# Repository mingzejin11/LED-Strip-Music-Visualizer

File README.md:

# LED-Strip-Music-Visualizer
Converting some boring LED strips into a party starter :)

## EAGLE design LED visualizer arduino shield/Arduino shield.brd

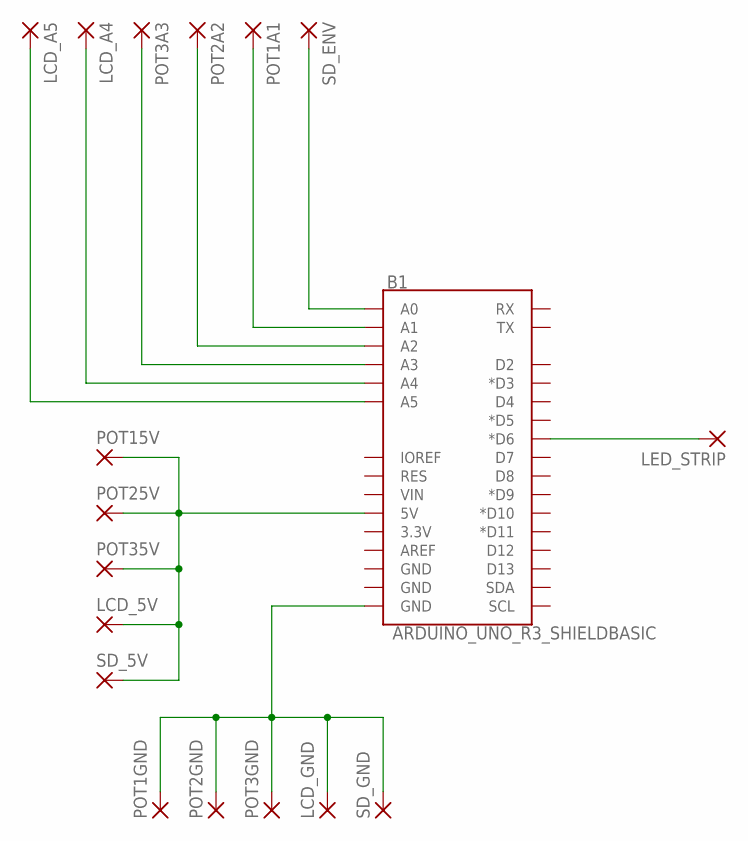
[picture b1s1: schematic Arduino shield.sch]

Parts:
B1: ARDUINO_UNO_R3_SHIELDBASIC; UNO_R3_SHIELD
LCD_5V: 1,6/0,9
LCD_A4, LCD_A5: 1,6/0,9
LCD_GND: 1,6/0,9
LED_STRIP: 1,6/0,9
POT1A1, POT1GND, POT2A2, POT2GND, POT3A3, POT3GND, POT15V, POT25V, POT35V: 1,6/0,9
SD_5V: 1,6/0,9
SD_ENV: 1,6/0,9
SD_GND: 1,6/0,9

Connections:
unnamed: B1.A0, SD_ENV.1
unnamed: B1.A1, POT1A1.1
unnamed: B1.A2, POT2A2.1
unnamed: B1.A3, POT3A3.1
unnamed: B1.A4, LCD_A4.1
unnamed: B1.A5, LCD_A5.1
unnamed: B1.GND@0 (GND), LCD_GND.1, POT1GND.1, POT2GND.1, POT3GND.1, SD_GND.1
unnamed: B1.5V, LCD_5V.1, POT15V.1, POT25V.1, POT35V.1, SD_5V.1
unnamed: B1.D6 (*D6), LED_STRIP.1

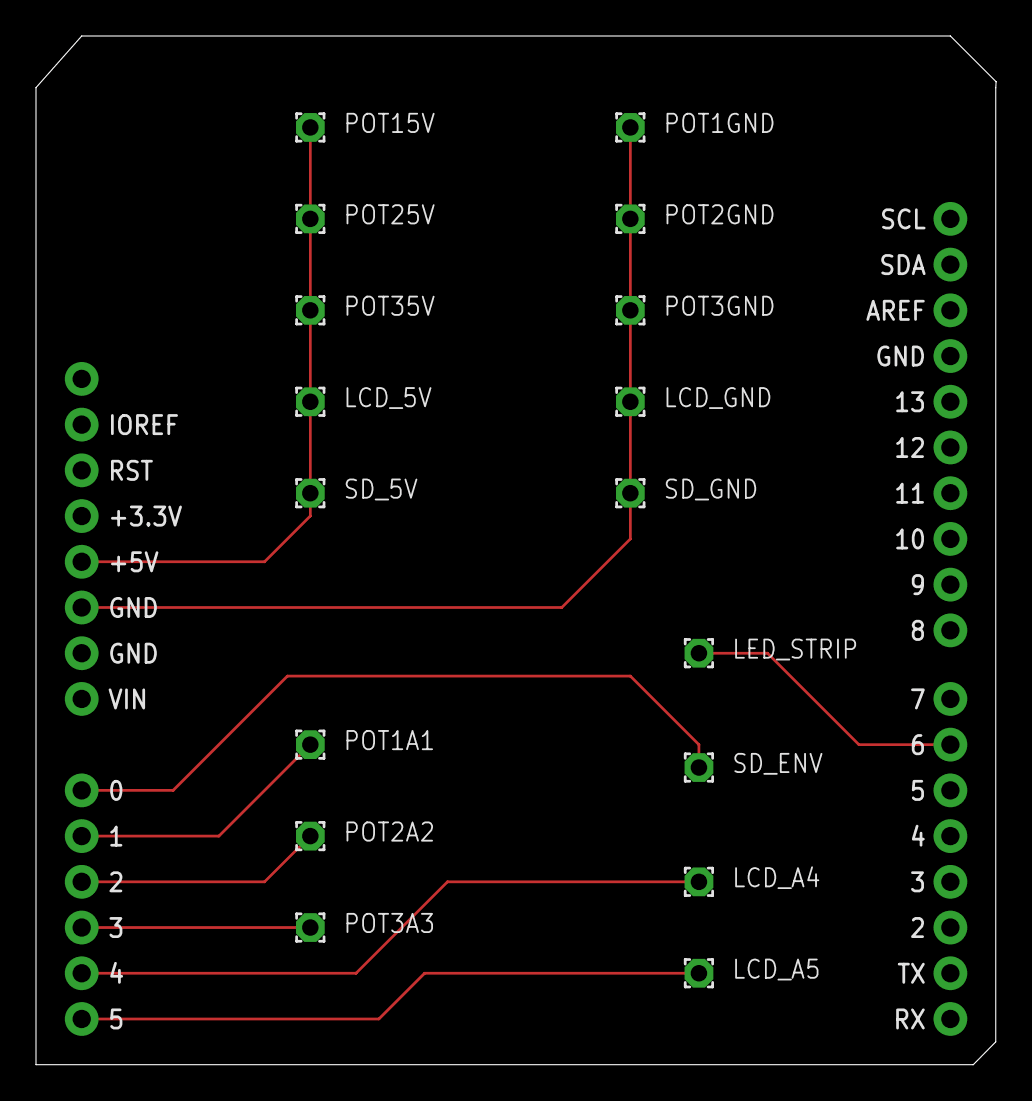
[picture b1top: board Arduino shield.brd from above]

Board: 2 copper layers, 53.3 x 57.1 mm, 18 parts (0 on the bottom side), 9 nets.

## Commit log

2020-05-19 Adding code file
2020-05-20 adding PCB files to project repo
2020-07-16 fixing some file changes

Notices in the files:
parts and their libraries:
SparkFun-Boards: Licensing: Creative Commons ShareAlike 4.0 International - https://creativecommons.org/licenses/by-sa/4.0
